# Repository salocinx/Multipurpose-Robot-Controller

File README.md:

# Multipurpose-Robot-Controller

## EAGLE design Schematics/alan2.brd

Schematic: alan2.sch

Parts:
ANALOG: PINHD-1X11; 1X11
ATMEGA: ARDUINO_MEGA_PINOUT
AUDIO_IN: AUDIOJACK
C1, C20: 220nF; C050-035X075
C2, C21: 2.2nF; C050-035X075
C3, C22: 47nF; C050-035X075
C4, C23: 22nF; C050-035X075
C5, C24: 150nF; C050-035X075
C6, C16, C25, C27: 1000uF; E5-13
C7, C9, C13, C14, C34, C35: 220uF; E5-8,5
C8, C10, C11, C12, C31, C32, C33, C36, C37: 10uF; C050-035X075
C15, C17, C26, C28: 100nF; C050-035X075
C18, C29: 33nF; C050-035X075
C19, C30: 470uF; E5-10,5
C38: 100uF; E2,5-5
D1, D3, D7: UF4004; DO41-7.6
D2, D4, D8: SR504; DO41-7.6
D5, D6: 1N4936; DO41-10
DIGITAL: PINHD-1X6; 1X06
ENABLE_1, ENABLE_2: PINHD-1X2; 1X02
ENV@D22: PINHD-1X3; 1X03
GPS@D40: PINHD-1X4; 1X04
GYROSCOPE@I2C: GYROSCOPE
I2C: PINHD-1X4; 1X04
IC1, IC5: TDA2003; PENTAWATT-V
IC2, IC3, IC4: LM2596S; TO263-5
IR_RECV@D48: TSOP1838
L1, L2, L3: 33uH; SFT830D
LED@D39, LED@D41, LED@D43, LED@D45, LED@D47: LED5MM
LIGHT@A1: PINHD-1X3; 1X03
MAINSWITCH: PINHD-1X2; 1X02
POWER: 12V / 9A; SCD-014-A
POWER_1, POWER_2: TERMINAL_BLOCK
R1, R23: 5K6?; 0204/7
R2, R24: 47K; 0204/7
R3, R25: 2.7K; 0204/7
R4, R26: 1R; 0204/7
R5, R11, R12, R13, R14, R15, R27: 220R; 0204/7
R6, R28: 39R; 0204/7
R7, R20, R30: ?; 0204/7
R8, R21, R31: 470R; 0204/7
R9: 1M; 0207/7
R10: 390K; 0207/7
R16, R17: 2K2; 0207/7
R18: 4K7; 0204/7
R19: 10K; 0204/7
R22, R29: 2R2; 0204/7
R32: 100R; 0204/7
R33: 20K; 0204/7
SENSOR@A2, SENSOR@A3, SENSOR@A4, SENSOR@A5: PINHD-1X3; 1X03
SERIAL: PINHD-1X12; 1X12
SERVO@D2, SERVO@D3, SERVO@D4, SERVO@D5, SERVO@D6, SERVO@D7, SERVO@D8, SERVO@D9, SERVO@D10, SERVO@D11: PINHD-1X3; 1X03
SONIC@D22, SONIC@D24, SONIC@D26, SONIC@D28, SONIC@D30, SONIC@D32, SONIC@D34, SONIC@D36: PINHD-1X4; 1X04
SPEAKER_1, SPEAKER_2: TERMINAL_BLOCK
T1, T2: BD239; TO220
TR2, TR4: 100K; PT-10
TR5, TR6, TR7: 10K; PT-10
U$2: POTI_STEREO
VOUT_1, VOUT_2, VOUT_3: TERMINAL_BLOCK

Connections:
+3.3V: ATMEGA.+3.3V, GPS@D40.4, R19.1
+5V0: ATMEGA.+5V0, GYROSCOPE@I2C.VCC, I2C.4, R32.1, R33.1, SERIAL.4, SERIAL.8, SERIAL.12
+5V1: ATMEGA.+5V1
+5V2: ATMEGA.+5V2, ENV@D22.2, LIGHT@A1.2, SENSOR@A2.2, SENSOR@A3.2, SENSOR@A4.2, SENSOR@A5.2, SONIC@D22.1, SONIC@D24.1, SONIC@D26.1, SONIC@D28.1, SONIC@D30.1, SONIC@D32.1, SONIC@D34.1, SONIC@D36.1
+12V: C7.+, C8.2, C12.2, C14.+, C33.2, C35.+, D1.C, D3.C, D5.A, D6.A, D7.C, IC2.1 (VIN), IC3.1 (VIN), IC4.1 (VIN), MAINSWITCH.1, R9.2
A0: ATMEGA.A0, R9.1, R10.1
A1: ATMEGA.A1, LIGHT@A1.3
A2: ATMEGA.A2, SENSOR@A2.3
A3: ATMEGA.A3, SENSOR@A3.3
A4: ATMEGA.A4, SENSOR@A4.3
A5: ATMEGA.A5, SENSOR@A5.3
A6: ANALOG.1, ATMEGA.A6
A7: ANALOG.2, ATMEGA.A7
A8: ANALOG.3, ATMEGA.A8
A9: ANALOG.4, ATMEGA.A9
A10: ANALOG.5, ATMEGA.A10
A11: ANALOG.6, ATMEGA.A11
A12: ANALOG.7, ATMEGA.A12
A13: ANALOG.8, ATMEGA.A13
A14: ANALOG.9, ATMEGA.A14
A15: ANALOG.10, ATMEGA.A15
D2: ATMEGA.D2, SERVO@D2.1
D3: ATMEGA.D3, SERVO@D3.1
D4: ATMEGA.D4, SERVO@D4.1
D5: ATMEGA.D5, SERVO@D5.1
D6: ATMEGA.D6, SERVO@D6.1
D7: ATMEGA.D7, SERVO@D7.1
D8: ATMEGA.D8, SERVO@D8.1
D9: ATMEGA.D9, SERVO@D9.1
D10: ATMEGA.D10, SERVO@D10.1
D11: ATMEGA.D11, SERVO@D11.1
D12: ATMEGA.D12
D13: ATMEGA.D13
D22: ATMEGA.D22, ENV@D22.3, SONIC@D22.3
D23: ATMEGA.D23, SONIC@D22.2
D24: ATMEGA.D24, SONIC@D24.3
D25: ATMEGA.D25, SONIC@D24.2
D26: ATMEGA.D26, SONIC@D26.3
D27: ATMEGA.D27, SONIC@D26.2
D28: ATMEGA.D28, SONIC@D28.3
D29: ATMEGA.D29, SONIC@D28.2
D30: ATMEGA.D30, SONIC@D30.3
D31: ATMEGA.D31, SONIC@D30.2
D32: ATMEGA.D32, SONIC@D32.3
D33: ATMEGA.D33, SONIC@D32.2
D34: ATMEGA.D34, SONIC@D34.3
D35: ATMEGA.D35, SONIC@D34.2
D36: ATMEGA.D36, SONIC@D36.3
D37: ATMEGA.D37, SONIC@D36.2
D38: ATMEGA.D38
D39: ATMEGA.D39, R11.2
D40: ATMEGA.D40, R18.1
D41: ATMEGA.D41, R12.2
D42: ATMEGA.D42, GPS@D40.2
D43: ATMEGA.D43, R13.2
D44: ATMEGA.D44, R16.1
D45: ATMEGA.D45, R14.2
D46: ATMEGA.D46, R17.1
D47: ATMEGA.D47, R15.2
D48: ATMEGA.D48, IR_RECV@D48.SIG, R33.2
D49: ATMEGA.D49, DIGITAL.1
D50: ATMEGA.D50, DIGITAL.2
D51: ATMEGA.D51, DIGITAL.3
D52: ATMEGA.D52, DIGITAL.4
D53: ATMEGA.D53, DIGITAL.5
GND: ANALOG.11, ATMEGA.GND0, ATMEGA.GND1, ATMEGA.GND2, ATMEGA.GND3, ATMEGA.GND4, AUDIO_IN.GND, C2.1, C5.1, C6.-, C7.-, C8.1, C9.-, C10.1, C11.1, C12.1, C13.-, C14.-, C15.1, C21.1, C24.1, C25.-, C26.1, C31.1, C32.1, C33.1, C34.-, C35.-, C36.1, C37.1, C38.-, D1.A, D2.A, D3.A, D4.A, D7.A, D8.A, DIGITAL.6, ENV@D22.1, GPS@D40.1, GYROSCOPE@I2C.GND, I2C.1, IC1.3 (GND), IC2.3 (GND), IC2.5 (!ON!/OFF), IC3.3 (GND), IC3.5 (!ON!/OFF), IC4.3 (GND), IC4.5 (!ON!/OFF), IC5.3 (GND), IR_RECV@D48.GND, LED@D39.K (C), LED@D41.K (C), LED@D43.K (C), LED@D45.K (C), LED@D47.K (C), LIGHT@A1.1, POWER.2, POWER.3, R4.2, R8.2, R10.2, R21.2, R22.2, R26.2, R29.2, R31.2, SENSOR@A2.1, SENSOR@A3.1, SENSOR@A4.1, SENSOR@A5.1, SERIAL.1, SERIAL.5, SERIAL.9, SERVO@D2.3, SERVO@D3.3, SERVO@D4.3, SERVO@D5.3, SERVO@D6.3, SERVO@D7.3, SERVO@D8.3, SERVO@D9.3, SERVO@D10.3, SERVO@D11.3, SONIC@D22.4, SONIC@D24.4, SONIC@D26.4, SONIC@D28.4, SONIC@D30.4, SONIC@D32.4, SONIC@D34.4, SONIC@D36.4, SPEAKER_1.B, SPEAKER_2.B, T1.3 (E), T2.3 (E), TR2.3, TR4.3, U$2.LA (L1), U$2.RA (R1), VOUT_1.B, VOUT_2.B, VOUT_3.B
unnamed: MAINSWITCH.2, POWER.1
unnamed: C3.2, R1.2, R2.1, U$2.RB (R2)
unnamed: C6.+, C15.2, D5.C, IC5.5 (VCC)
unnamed: C1.2, IC5.1 (+IN)
unnamed: C3.1, TR2.1
unnamed: C4.2, R2.2
unnamed: C1.1, C2.2, C4.1, R3.1, U$2.RC (R3)
unnamed: C5.2, R3.2, TR2.2
unnamed: C16.+, C18.2, IC5.4 (OUT), R5.1
unnamed: C16.-, C17.2, SPEAKER_1.A
unnamed: C17.1, R4.1
unnamed: C19.-, R5.2, R22.1
unnamed: C18.1, R6.1
unnamed: ENABLE_1.2, POWER_1.A
unnamed: C19.+, IC5.2 (-IN), R6.2
unnamed: AUDIO_IN.LEFT, R1.1
unnamed: D4.C, IC3.2 (OUT), L2.1
unnamed: IC2.4 (FB), R7.2, R8.1, TR5.2
unnamed: D2.C, IC2.2 (OUT), L1.1
unnamed: R17.2, T1.1 (B)
unnamed: IC3.4 (FB), R20.2, R21.1, TR6.2
unnamed: ENABLE_2.2, POWER_2.A
unnamed: C22.2, R23.2, R24.1, U$2.LB (L2)
unnamed: D8.C, IC4.2 (OUT), L3.1
unnamed: POWER_2.B, T1.2 (C)
unnamed: GPS@D40.3, R18.2, R19.2
unnamed: AUDIO_IN.RIGHT, R23.1
unnamed: C38.+, IR_RECV@D48.VCC, R32.2
unnamed: LED@D47.A, R15.1
unnamed: LED@D45.A, R14.1
unnamed: LED@D43.A, R13.1
unnamed: LED@D41.A, R12.1
unnamed: LED@D39.A, R11.1
unnamed: R16.2, T2.1 (B)
unnamed: IC4.4 (FB), R30.2, R31.1, TR7.2
unnamed: C20.2, IC1.1 (+IN)
unnamed: C22.1, TR4.1
unnamed: C23.2, R24.2
unnamed: C20.1, C21.2, C23.1, R25.1, U$2.LC (L3)
unnamed: C24.2, R25.2, TR4.2
unnamed: C25.+, C26.2, D6.C, IC1.5 (VCC)
unnamed: C27.+, C29.2, IC1.4 (OUT), R27.1
unnamed: C27.-, C28.2, SPEAKER_2.A
unnamed: C28.1, R26.1
unnamed: POWER_1.B, T2.2 (C)
unnamed: C30.-, R27.2, R29.1
unnamed: C29.1, R28.1
unnamed: C30.+, IC1.2 (-IN), R28.2
RESET: ATMEGA.RESET
RX1: ATMEGA.RX1, SERIAL.2
RX2: ATMEGA.RX2, SERIAL.6
RX3: ATMEGA.RX3, SERIAL.10
SCL: ATMEGA.SCL1, GYROSCOPE@I2C.SCL, I2C.2
SDA: ATMEGA.SDA1, GYROSCOPE@I2C.SDA, I2C.3
TX1: ATMEGA.TX1, SERIAL.3
TX2: ATMEGA.TX2, SERIAL.7
TX3: ATMEGA.TX3, SERIAL.11
VOUT_3A_1: C9.+, C10.2, C11.2, ENABLE_1.1, L1.2, R7.1, TR5.1, TR5.3, VOUT_1.A
VOUT_3A_2: C13.+, C31.2, C32.2, ENABLE_2.1, L2.2, R20.1, SERVO@D7.2, SERVO@D8.2, SERVO@D9.2, SERVO@D10.2, SERVO@D11.2, TR6.1, TR6.3, VOUT_2.A
VOUT_3A_3: C34.+, C36.2, C37.2, L3.2, R30.1, SERVO@D2.2, SERVO@D3.2, SERVO@D4.2, SERVO@D5.2, SERVO@D6.2, TR7.1, TR7.3, VOUT_3.A

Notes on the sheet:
Voltage Converter (4.5-35V to 1.3-30V @ 3A)
Stereo Audio Amplifier (12V @ 10W)
Battery Condition Measurement (max 18V)
Battery Condition Indicator (5x LED)
Power Switch (Primary - max 3A)
Power Switch (Secondary - max 3A)
PWM
Servo Grid (Secondary)
Servo Grid (Primary)
VOUT_3A_2 can either be used to power the secondary servo grid OR to power the secondary power switch (e.g. for an IR LED array). Do not exceed 3A !
Sensor Grid
GPS Module
Gyroscope
Infrared Receiver
MRC R2 - POWER
Nicolas Baumgardt
Last Update: Year 2017
MRC R2 - STEREO AMPLIFIER
MRC R2 - SENSORS + ACTORS
MRC R2 - ATMEGA 2560

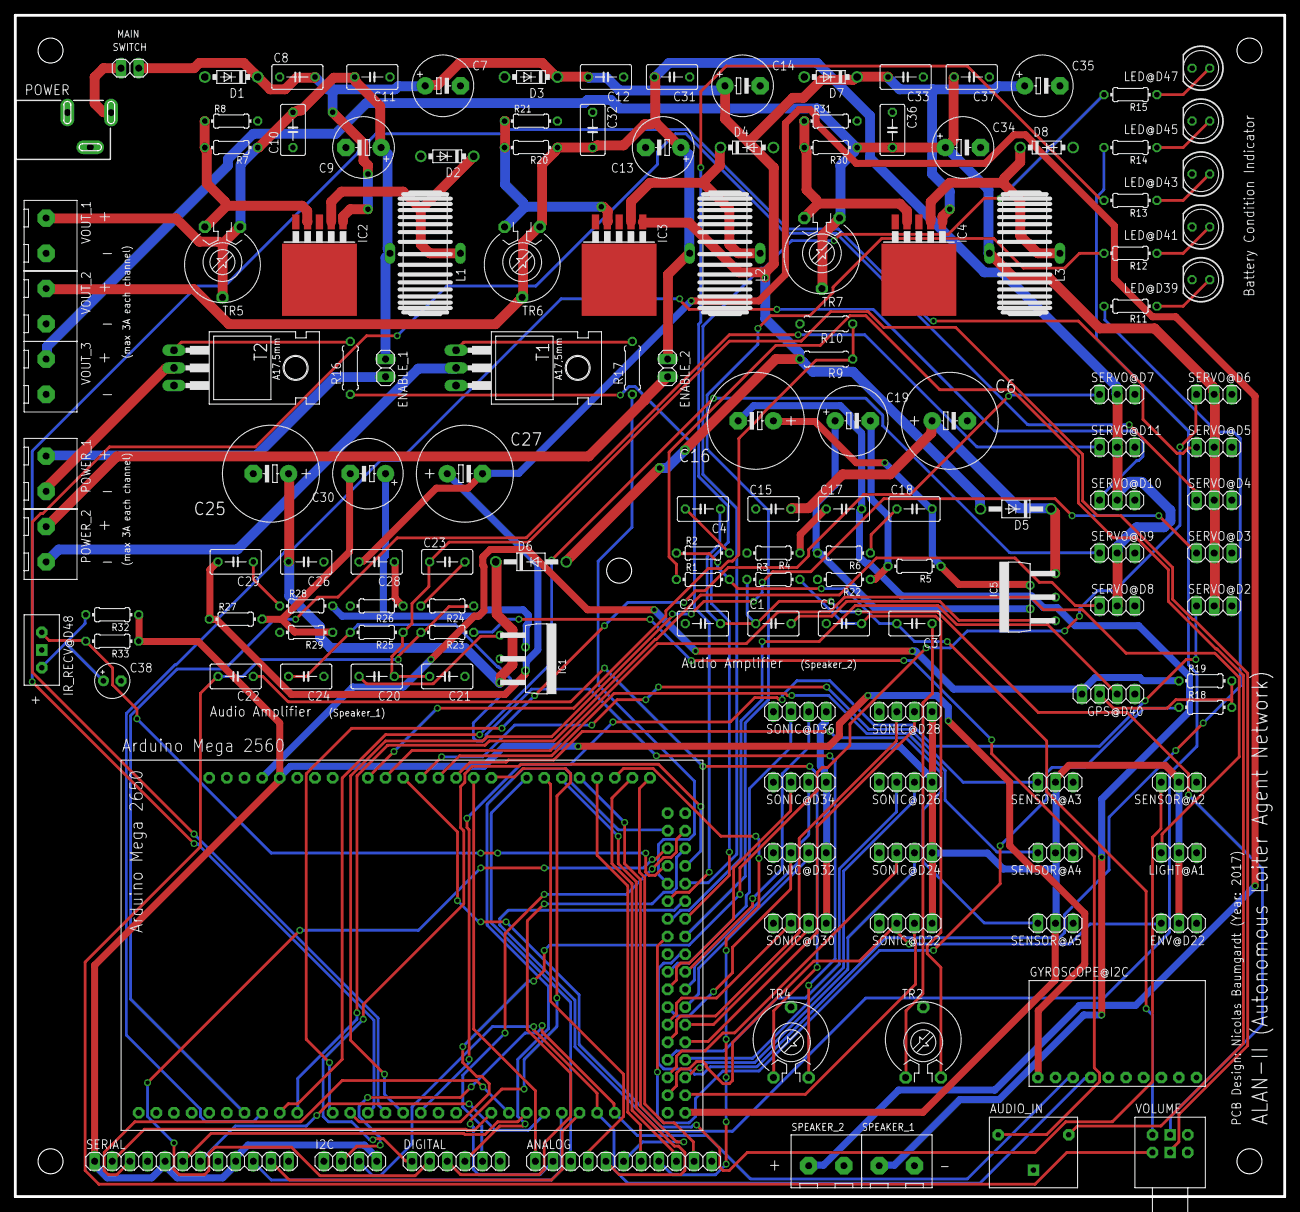
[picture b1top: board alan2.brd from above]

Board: 2 copper layers, 182.9 x 170.2 mm, 144 parts (0 on the bottom side), 121 nets.

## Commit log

2019-10-03 init
